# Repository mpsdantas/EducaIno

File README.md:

EducaIno - Simplificando a Robótica                   
===================

A placa EducaIno (Educação + Arduino) é um projeto de uma placa de circuito impresso open source que está sendo desenvolvido no Laboratório de Automação e Robótica da [Universidade Federal do Rio Grande do Norte](https://sistemas.ufrn.br/portal/PT/). Atualmente o projeto conta com alguns desenvolvedores sendo os mais ativos o Professor Doutor [Orivaldo Vieira De Santana Junior](https://sigaa.ufrn.br/sigaa/public/docente/portal.jsf?siape=1943220) e [Marcus Paulo Soares Dantas](http://marcuspaulo.esy.es/) Graduando do curso de Ciências e Tecnologia - Engenharia da Computação.

----------
Versões do EducaIno
-------------
**EducaIno 1.0**
</br>
</br>

Resultados de testes de uso:  ***REPROVADO**       
</br>
</br>
**EducaIno 1.1**
</br>
</br>

</br>
</br>
Resultados de testes de uso:  ***EM ANALISE** 

----------
Registro de melhorias
-------------
1.0 -> 1.1

 - Correção da ligação do pino de 5v incorreta, anteriormente conectado ao GND.
 - Dois conectores de sensores conectados corretamente a pinos de dados.
 - Pinos enable do l293D agora são ligados a pinos de dados.

----------

Universidade Federal do Rio Grande do Norte
-------------
A Universidade Federal do Rio Grande do Norte (UFRN) é uma instituição de ensino superior pública brasileira, com sede na cidade de Natal, no estado do Rio Grande do Norte. É a principal universidade do estado e uma das dez maiores universidades federais do Brasil em número de alunos de graduação matriculados. De acordo com o Índice Geral de Cursos, é a universidade mais bem avaliada no Rio Grande do Norte e das regiões Norte e Nordeste, com um total de 82,64 pontos, estando na 11ª posição entre as instituições de nível superior nacionais.
> **[Mais Informações sobre a UFRN](https://pt.wikipedia.org/wiki/Universidade_Federal_do_Rio_Grande_do_Norte)**

----------

EducaIno: Um robô por aluno
-------------------
<center></center>
</br>
O URA (Um robô por aluno) é um projeto dos pesquisadores do Laboratório NatalNet da Universidade Federal do Rio Grande do Norte (UFRN), que têm o objetivo de utilizar a robótica educacional para difundir o interesse por tecnologia em todos os níveis de ensino no País. 
Tendo em vista o potencial do projeto URA a placa EducaIno está sendo desenvolvida como uma forma de melhoria para esse projeto criando uma placa mais agradável e de fácil utilização para os alunos.
> **[Mais Informações sobre o URA](http://www.natalnet.br/ura/)**

----------

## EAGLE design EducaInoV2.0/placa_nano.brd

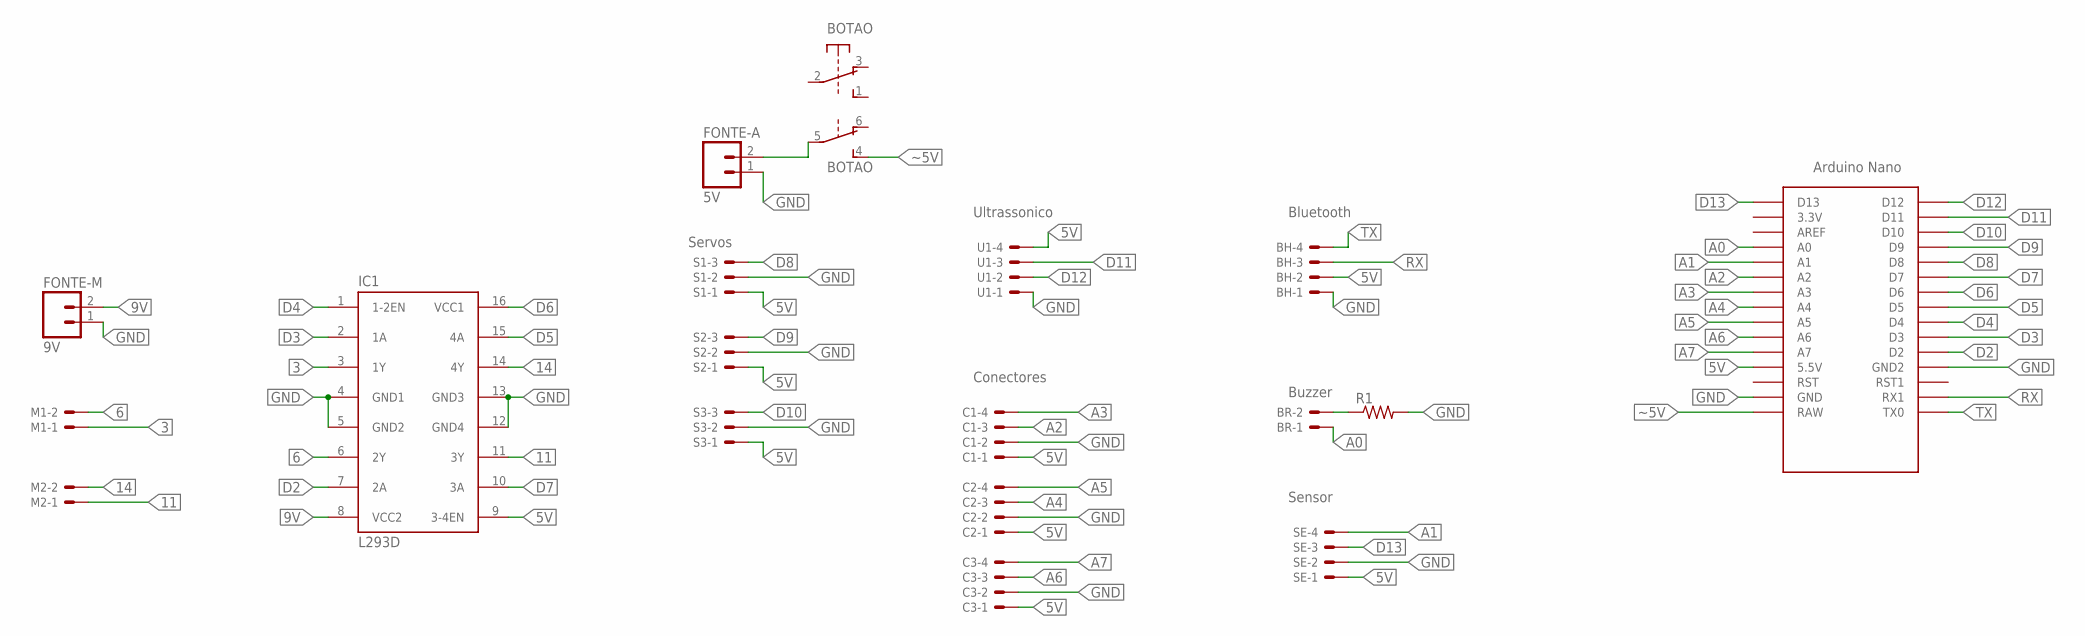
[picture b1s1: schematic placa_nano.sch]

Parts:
BH: 22-23-2041
BOTAO: 9077-2
BR: 22-23-2021
C1, C2, C3: 22-23-2041
FONTE-A: 5V; 02P
FONTE-M: 9V; 02P
IC1: L293D; DIL16
M1, M2: 22-23-2021
R1: R-US_0207/10; 0207/10
S1, S2, S3: 22-23-2031
SE: 22-23-2041
U1: 22-23-2041
U$1: NANO

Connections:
3: IC1.3 (1Y), M1.1
5V: BH.2, C1.1, C2.1, C3.1, IC1.9 (3-4EN), S1.1, S2.1, S3.1, SE.1, U1.4, U$1.5V (5.5V)
6: IC1.6 (2Y), M1.2
9V: FONTE-M.2, IC1.8 (VCC2)
11: IC1.11 (3Y), M2.1
14: IC1.14 (4Y), M2.2
A0: BR.1, U$1.A0
A1: SE.4, U$1.A1
A2: C1.3, U$1.A2
A3: C1.4, U$1.A3
A4: C2.3, U$1.A4
A5: C2.4, U$1.A5
A6: C3.3, U$1.A6
A7: C3.4, U$1.A7
D2: IC1.7 (2A), U$1.D2
D3: IC1.2 (1A), U$1.D3
D4: IC1.1 (1-2EN), U$1.D4
D5: IC1.15 (4A), U$1.D5
D6: IC1.16 (VCC1), U$1.D6
D7: IC1.10 (3A), U$1.D7
D8: S1.3, U$1.D8
D9: S2.3, U$1.D9
D10: S3.3, U$1.D10
D11: U1.3, U$1.D11
D12: U1.2, U$1.D12
D13: SE.3, U$1.D13
GND: BH.1, C1.2, C2.2, C3.2, FONTE-A.1, FONTE-M.1, IC1.4 (GND1), IC1.5 (GND2), IC1.12 (GND4), IC1.13 (GND3), R1.2, S1.2, S2.2, S3.2, SE.2, U1.1, U$1.GND, U$1.GND1 (GND2)
unnamed: BR.2, R1.1
RX: BH.3, U$1.RX1
TX: BH.4, U$1.TX0
~5V: BOTAO.4 (S), BOTAO.5, FONTE-A.2, U$1.RAW

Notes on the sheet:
Servos
Ultrassonico
Bluetooth
Buzzer
Sensor
Conectores

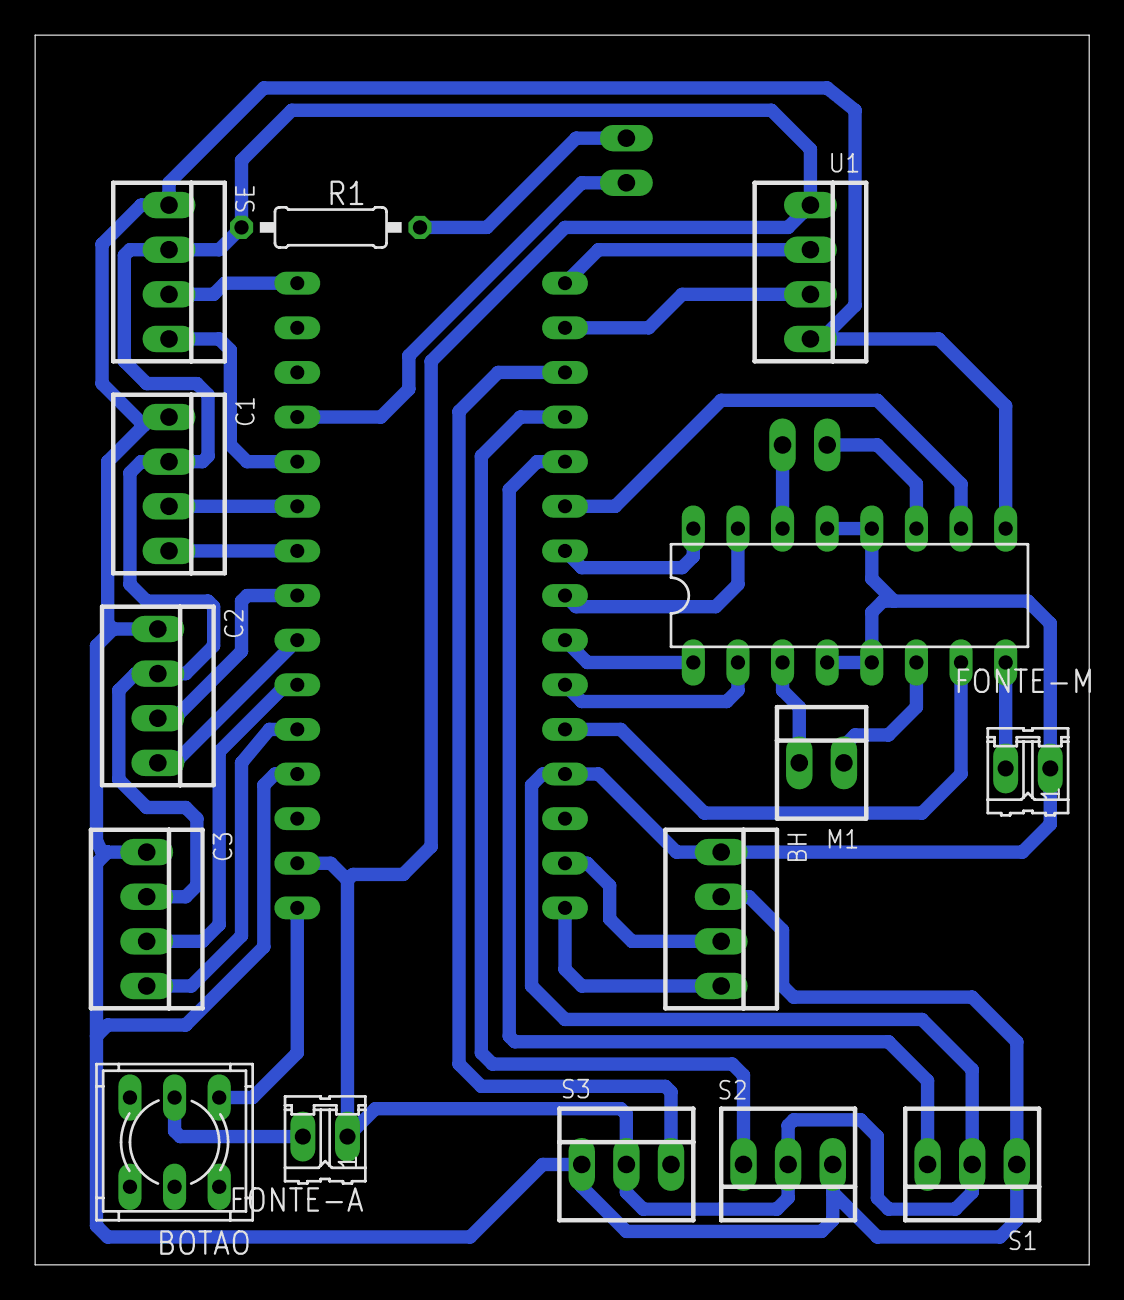
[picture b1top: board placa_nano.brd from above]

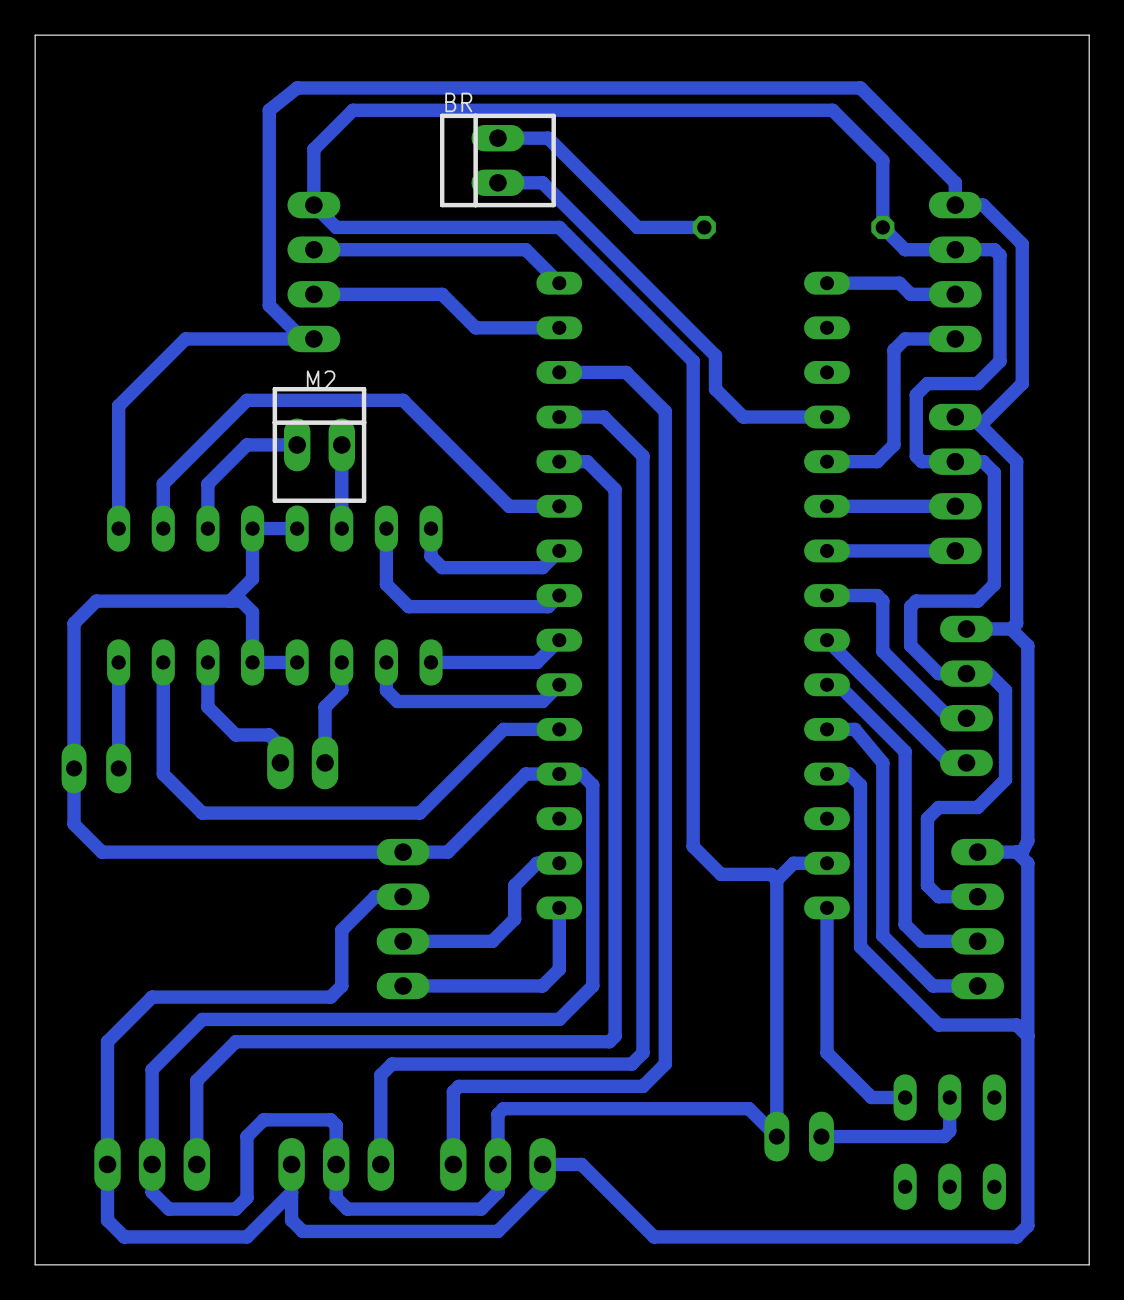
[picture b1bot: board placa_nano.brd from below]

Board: 2 copper layers, 60.0 x 70.0 mm, 18 parts (2 on the bottom side), 31 nets.

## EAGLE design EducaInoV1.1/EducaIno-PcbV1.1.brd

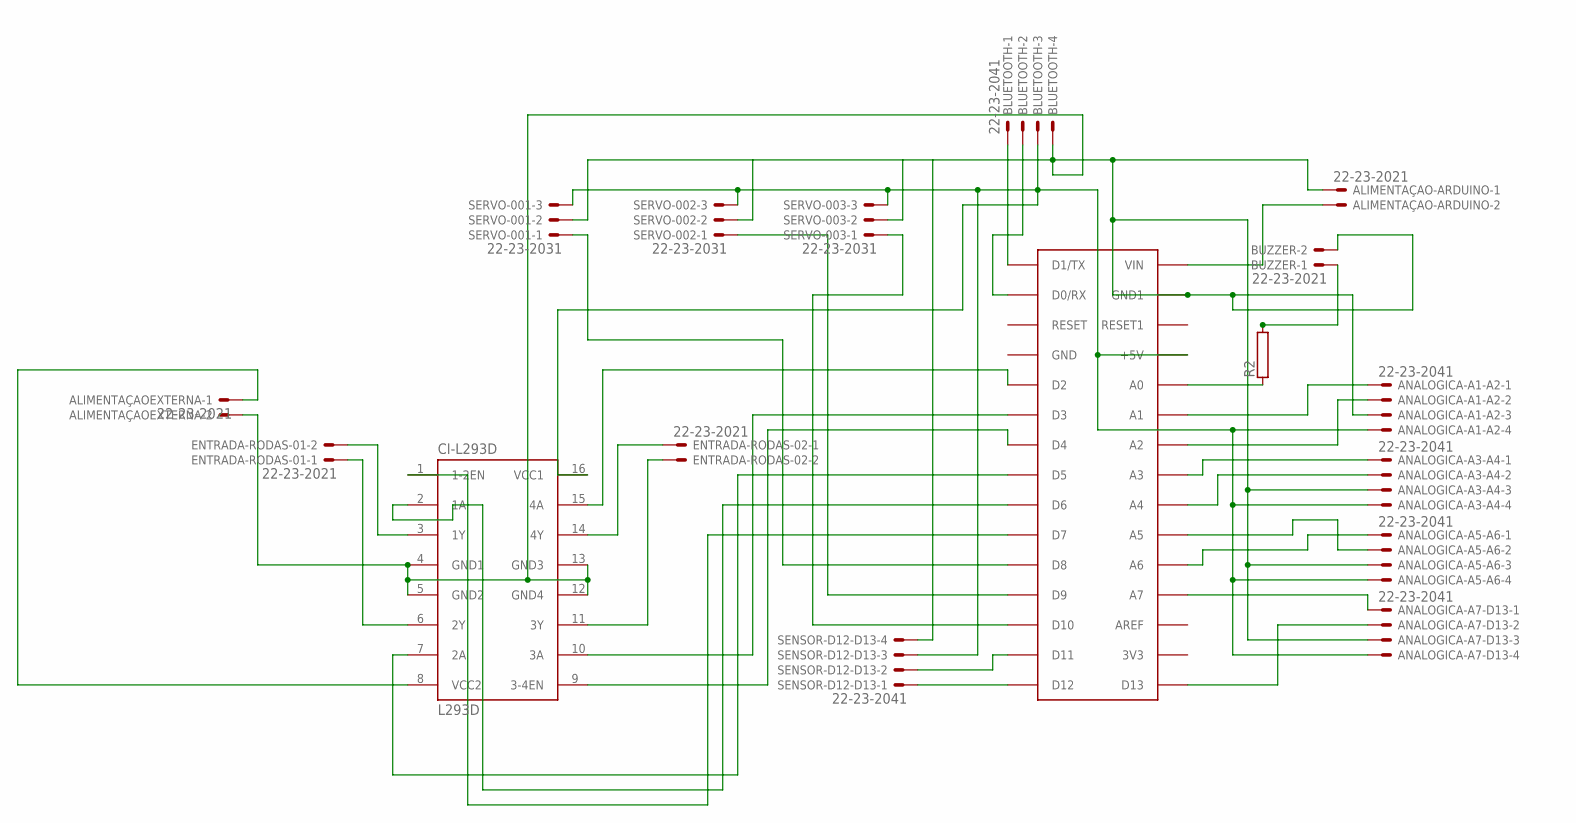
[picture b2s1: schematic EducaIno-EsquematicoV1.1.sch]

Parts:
ALIMENTAÇAO-ARDUINO: 22-23-2021
ALIMENTAÇAOEXTERNA: 22-23-2021
ANALOGICA-A1-A2, ANALOGICA-A3-A4, ANALOGICA-A5-A6, ANALOGICA-A7-D13: 22-23-2041
BLUETOOTH: 22-23-2041
BUZZER: 22-23-2021
CI-L293D: L293D; DIL16
ENTRADA-RODAS-01, ENTRADA-RODAS-02: 22-23-2021
R2: RHPS58; HPS58
SENSOR-D12-D13: 22-23-2041
SERVO-001, SERVO-002, SERVO-003: 22-23-2031
U$1: ARDUINONANO; PDIP-32

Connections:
unnamed: CI-L293D.1 (1-2EN), U$1.D7
unnamed: CI-L293D.3 (1Y), ENTRADA-RODAS-01.2
unnamed: ALIMENTAÇAO-ARDUINO.1, ALIMENTAÇAOEXTERNA.2, ANALOGICA-A1-A2.3, ANALOGICA-A3-A4.3, ANALOGICA-A5-A6.3, ANALOGICA-A7-D13.3, BLUETOOTH.4, BUZZER.2, CI-L293D.4 (GND1), CI-L293D.5 (GND2), CI-L293D.12 (GND4), CI-L293D.13 (GND3), SENSOR-D12-D13.4, SERVO-001.2, SERVO-002.2, SERVO-003.2, U$1.GND1
unnamed: ALIMENTAÇAOEXTERNA.1, CI-L293D.8 (VCC2)
unnamed: CI-L293D.6 (2Y), ENTRADA-RODAS-01.1
unnamed: CI-L293D.14 (4Y), ENTRADA-RODAS-02.1
unnamed: CI-L293D.11 (3Y), ENTRADA-RODAS-02.2
unnamed: CI-L293D.2 (1A), U$1.D6
unnamed: CI-L293D.7 (2A), U$1.D5
unnamed: CI-L293D.15 (4A), U$1.D2
unnamed: CI-L293D.10 (3A), U$1.D3
unnamed: CI-L293D.9 (3-4EN), U$1.D4
unnamed: SERVO-001.1, U$1.D8
unnamed: SERVO-002.1, U$1.D9
unnamed: SERVO-003.1, U$1.D10
unnamed: ALIMENTAÇAO-ARDUINO.2, U$1.VIN
unnamed: BUZZER.1, R2.2
unnamed: R2.1, U$1.A0
unnamed: ANALOGICA-A1-A2.1, U$1.A1
unnamed: ANALOGICA-A1-A2.2, U$1.A2
unnamed: ANALOGICA-A3-A4.1, U$1.A3
unnamed: ANALOGICA-A3-A4.2, U$1.A4
unnamed: ANALOGICA-A5-A6.2, U$1.A5
unnamed: ANALOGICA-A5-A6.1, U$1.A6
unnamed: ANALOGICA-A7-D13.1, U$1.A7
unnamed: ANALOGICA-A7-D13.2, U$1.D13
unnamed: BLUETOOTH.1, U$1.D1/TX
unnamed: BLUETOOTH.2, U$1.D0/RX
S$1: U$1.GND
S$3: SENSOR-D12-D13.2, U$1.D11
S$4: SENSOR-D12-D13.1, U$1.D12

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
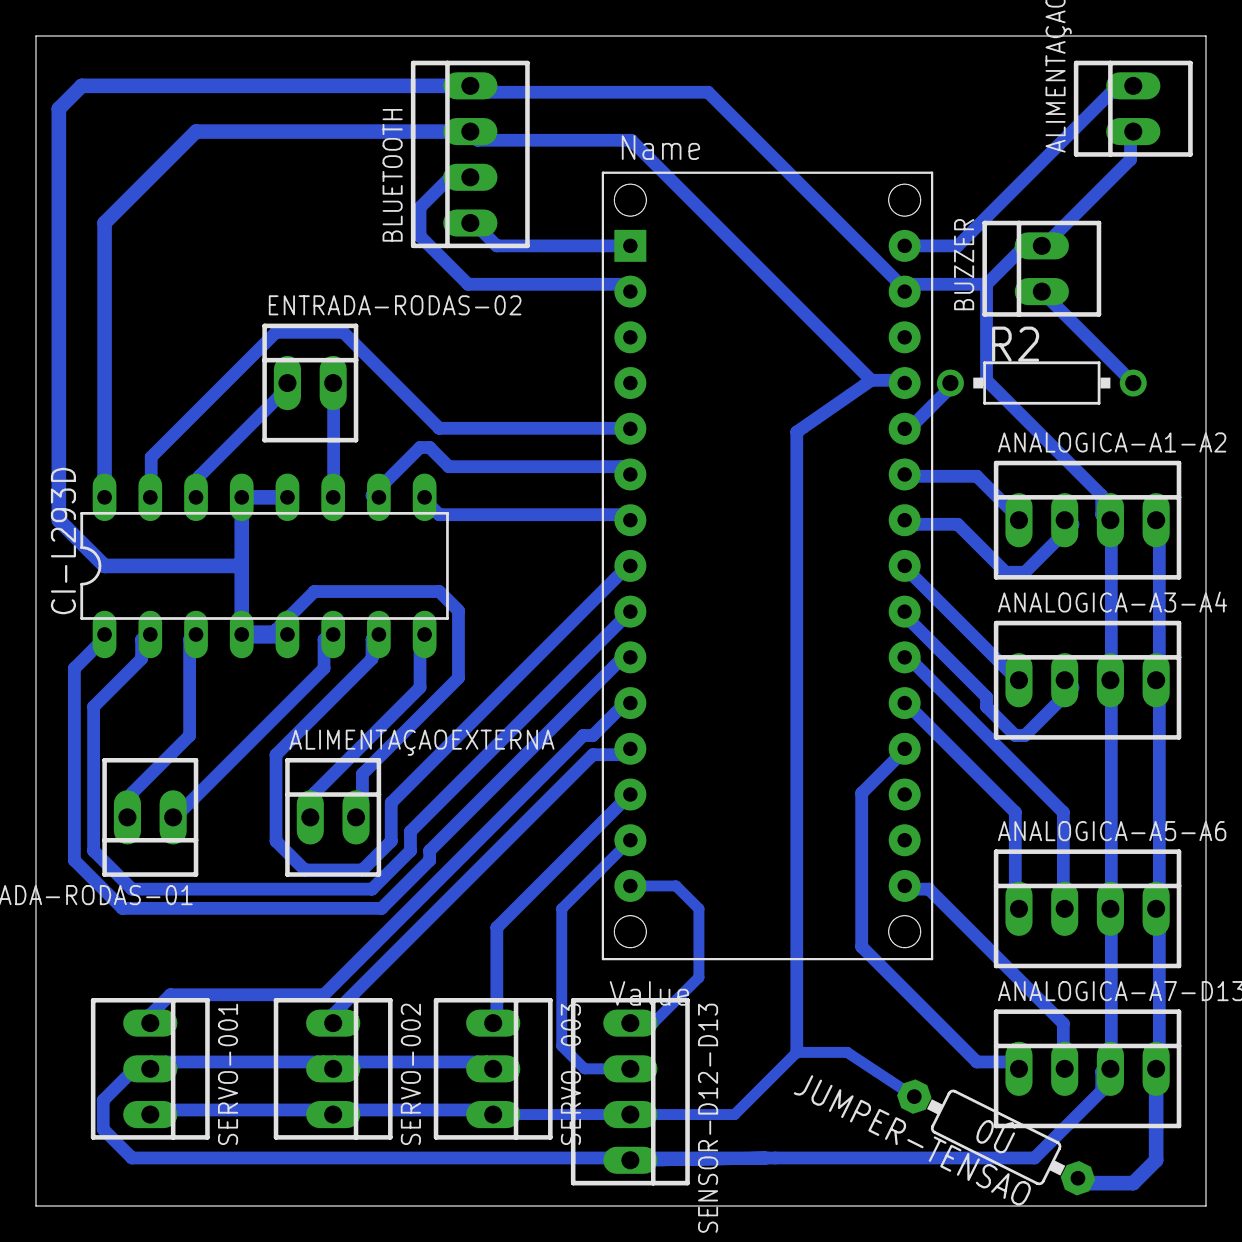
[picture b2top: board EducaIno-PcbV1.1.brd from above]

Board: 2 copper layers, 65.0 x 65.0 mm, 18 parts (0 on the bottom side), 32 nets.

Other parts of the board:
JUMPER-TENSAO: 0R/10E

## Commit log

2016-08-08 Placa funcional EducaIno versão 01
2016-08-08 Alteração de nomeclatura dos arquivos e criação de vizualização em png da placa.
2016-08-15 Placa nova criada no eagle.
2016-08-15 Motivo de parada de utilização do fritzing
2016-08-15 Modificação de nome das pastas do EducaIno.
2016-08-17 Servos adicionados
2016-08-17 Adicionados componentes que faltavam (bluetooth e slots para outros sensores), o esquematico foi finalizado
2016-08-17 Adicionado figura para visualizar o esquematico
2016-08-17 Esquematico Final.
2016-08-17 Esquematico final da placa V2
2016-08-17 Imagem adicionada da pcb da placa.
2016-08-18 Atualização de esquema de pastas
2016-08-18 Correção de terra do pino l293d que não estava conectado corretamente.
2016-08-18 Correção da ligação do terra do ci l293d.
2016-08-18 Correção de trilha do terra para exibição
2016-08-18 Remoção esquematico
2016-08-18 arquivos deletados
2016-08-18 Esquematico placa v1.1
2016-08-18 Pcb placa v1.1
2016-08-28 Modificação de pinos modu para conexão do cabo usb
2016-09-16 Código de movimentação simples para robô com sensor ultrassônico.
2017-05-19 Placa versão 2.0
